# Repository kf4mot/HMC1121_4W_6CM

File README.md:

# HMC1121 4W 6cm
The HMC1121 is a GaAs MMIC 4W power amplifier with an integrated temperature compensated on-chip power detector that operates between 5.5 GHz and 8.5 GHz. The HMC1121 provides 28 dB of gain, 44 dBm output IP3, and 36.5 dBm of saturated output power at 30% PAE from a 7 V power supply.

[Schematic](https://github.com/kf4mot/HMC1121_4W_6CM/blob/master/hardware/HMC1121_4W_6CM.pdf)

[Created with KiCAD ver. 5.1.5-3](https://kicad.org)

[Companion bias board.](https://github.com/kf4mot/Cree_GaN_Driver)

**Things to be done**
- [ ] Add all documentation
- [ ] Revise board for 50Ω traces on better substrate (ro4350).

**Things worth knowing**

1. -To be added.

[Licensed under CERN-OHL-S V2. Julian White, 2020](https://www.ohwr.org/project/cernohl/wikis/home)

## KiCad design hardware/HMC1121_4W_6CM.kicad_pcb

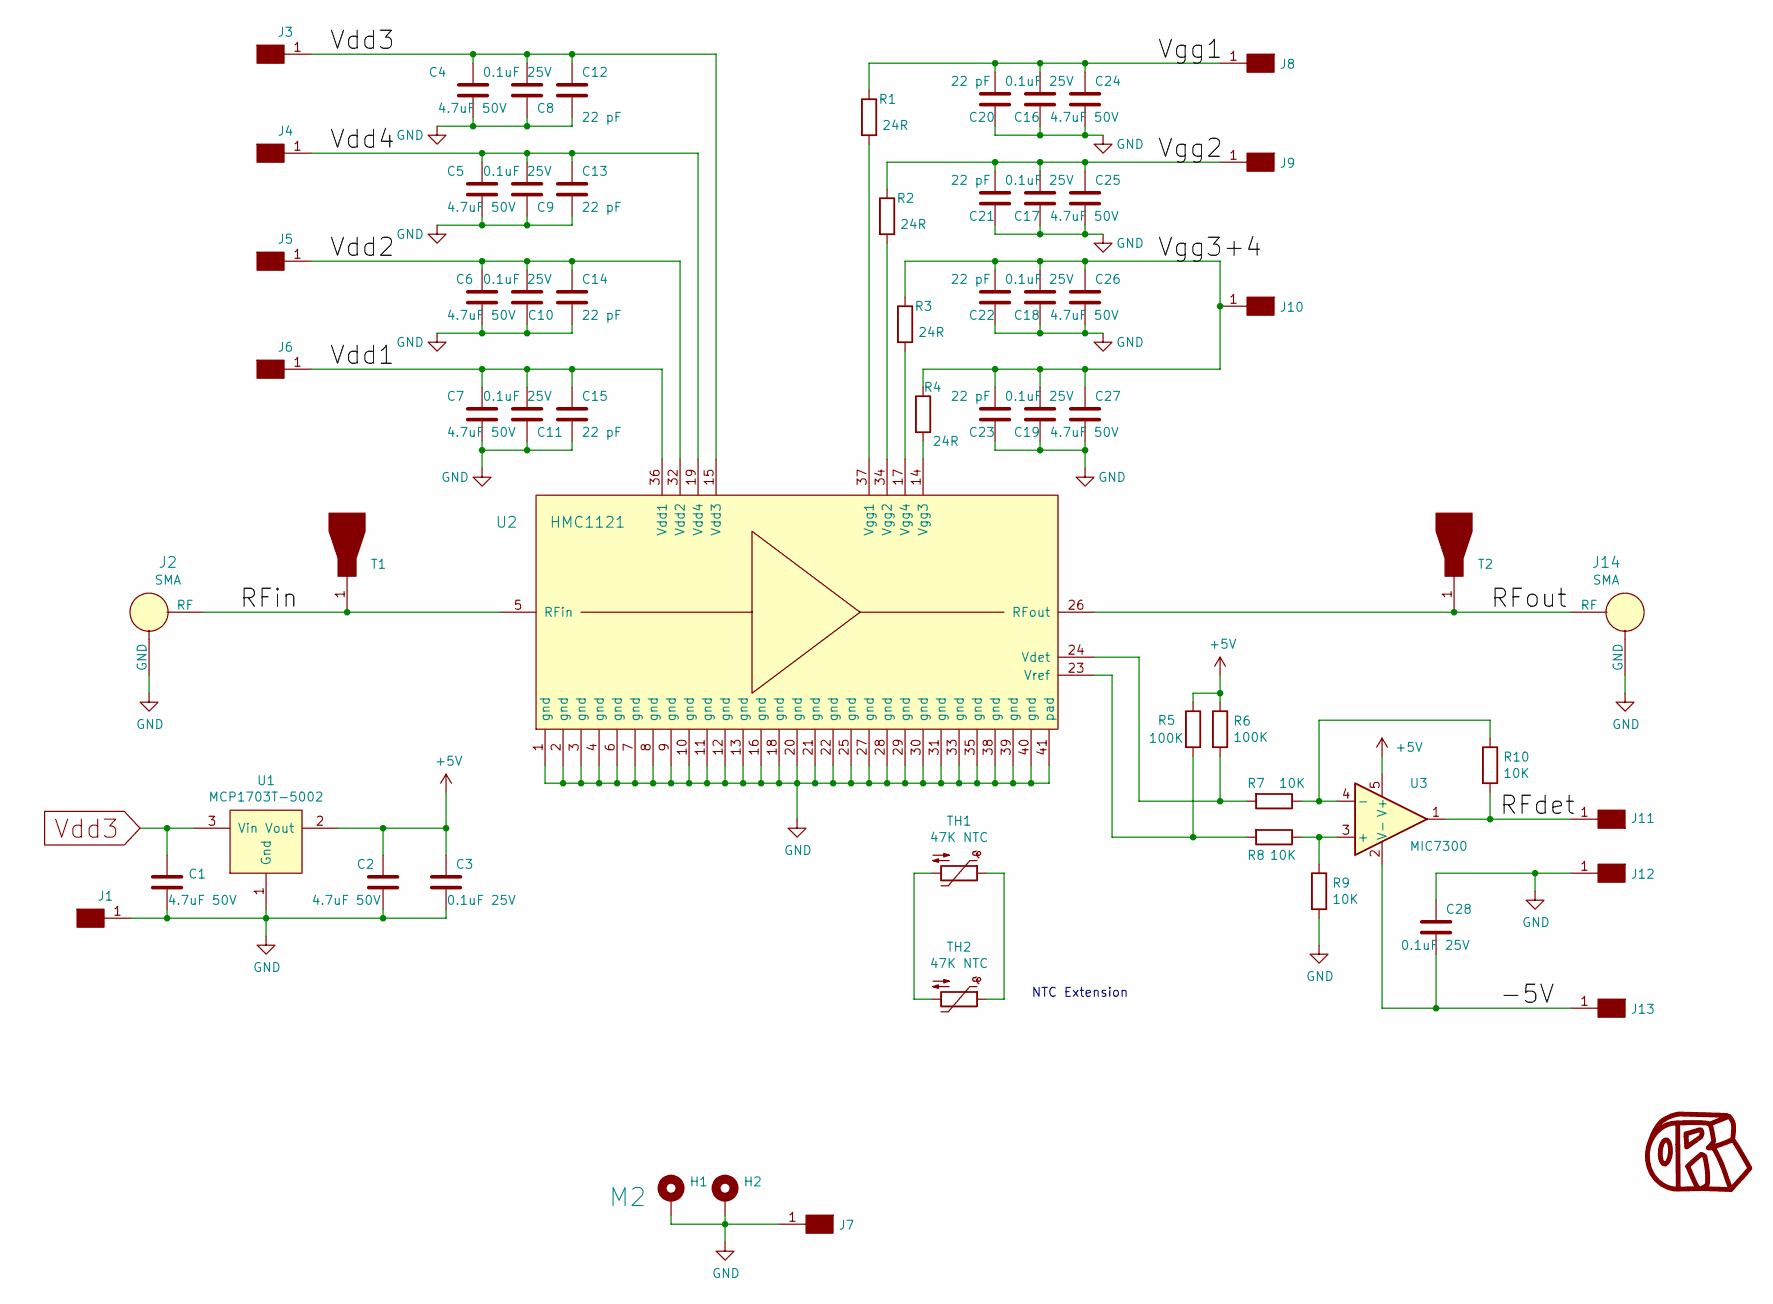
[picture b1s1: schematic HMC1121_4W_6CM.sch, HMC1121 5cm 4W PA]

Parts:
C1, C2, C4, C5, C6, C7, C24, C25, C26, C27: C_4.7uf_50V_x7r_1206; C_1206_3216Metric; Part Number GRM31CR71H475KA12L
C3, C8, C9, C10, C11, C20, C21, C22, C23, C28: 0.1uF_25V_0402_x7r; C_0402_1005Metric; Part Number CGA2B3X7R1E104K050BB
C12, C13, C14, C15, C16, C17, C18, C19: C_22pF_0402_50V_C0G; C_0402_1005Metric; Part Number GRM1555C1H220JA01D
H1, H2: MountingHole_Pad_M2; MountingHole_2.2mm_M2_DIN965_Pad
J1, J3, J4, J5, J6, J7, J8, J9, J10, J11, J12, J13: Conn_4mm_pad; SolderWirePad_single_SMD_4mm
J2, J14: SMA_F_Amp_901-10309; SMA_END_LAUNCH_062_AMP901-10309; Part Number 901-10309
R1, R2, R3, R4: R_24_sm0603; R_0603_1608Metric; Part Number RT0603FRE0724RL
R5, R6: R_100k_sm0603; R_0603; Part Number RT0603FRE07100KL
R7, R8, R9, R10: R_10K_sm0603; R_0603_1608Metric; Part Number RT0603FRE0710KL
T1, T2: Taper_45mil_to_12mil; Taper_45to12_uwT1.14_1.14_0.30_0.30_2.00
TH1, TH2: Thermistor_NTC_ERT-J1VV473J; R_0603_1608Metric; Part Number ERT-J1VV473J
U1: MCP1703T-5002; SOT-23; Part Number MCP1703T-5002E/CB
U2: HMC1121; LFCSP-40-1EP; Part Number HMC1121LP6GE
U3: MIC7300; SOT-23-5; Part Number MIC7300YM5-TR

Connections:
+5V: C2.1, C3.1, R5.1, R6.1, U1.2 (Vout), U3.5 (V+)
/-5V: C28.2, J13.1, U3.2 (V-)
/RFdet: J11.1, R10.2, U3.1
/RFin: J2.1 (RF), T1.1, U2.5 (RFin)
/RFout: J14.1 (RF), T2.1, U2.26 (RFout)
/Vdd1: C7.1, C11.1, C15.1, J6.1, U2.36 (Vdd1)
/Vdd2: C6.1, C10.1, C14.1, J5.1, U2.32 (Vdd2)
/Vdd4: C5.1, C9.1, C13.1, J4.1, U2.19 (Vdd4)
/Vgg1: C16.1, C20.1, C24.1, J8.1, R1.1
/Vgg2: C17.1, C21.1, C25.1, J9.1, R2.1
/Vgg3+4: C18.1, C19.1, C22.1, C23.1, C26.1, C27.1, J10.1, R3.1, R4.1
GND: C1.2, C2.2, C3.2, C4.2, C5.2, C6.2, C7.2, C8.2, C9.2, C10.2, C11.2, C12.2, C13.2, C14.2, C15.2, C16.2, C17.2, C18.2, C19.2, C20.2, C21.2, C22.2, C23.2, C24.2, C25.2, C26.2, C27.2, C28.1, H1.1, H2.1, J1.1, J2.2 (GND), J7.1, J12.1, J14.2 (GND), R9.2, U1.1 (Gnd), U2.1 (gnd), U2.2 (gnd), U2.3 (gnd), U2.4 (gnd), U2.6 (gnd), U2.7 (gnd), U2.8 (gnd), U2.9 (gnd), U2.10 (gnd), U2.11 (gnd), U2.12 (gnd), U2.13 (gnd), U2.16 (gnd), U2.18 (gnd), U2.20 (gnd), U2.21 (gnd), U2.22 (gnd), U2.25 (gnd), U2.27 (gnd), U2.28 (gnd), U2.29 (gnd), U2.30 (gnd), U2.31 (gnd), U2.33 (gnd), U2.35 (gnd), U2.38 (gnd), U2.39 (gnd), U2.40 (gnd), U2.41 (pad)
unnamed: R1.2, U2.37 (Vgg1)
unnamed: R2.2, U2.34 (Vgg2)
unnamed: R3.2, U2.17 (Vgg4)
unnamed: R4.2, U2.14 (Vgg3)
unnamed: R5.2, R8.2, U2.23 (Vref)
unnamed: R6.2, R7.2, U2.24 (Vdet)
unnamed: R8.1, R9.1, U3.3 (+)
unnamed: R7.1, R10.1, U3.4 (-)
unnamed: TH1.1, TH2.1
unnamed: TH1.2, TH2.2
Vdd3: C1.1, C4.1, C8.1, C12.1, J3.1, U1.3 (Vin), U2.15 (Vdd3)

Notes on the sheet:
NTC Extension

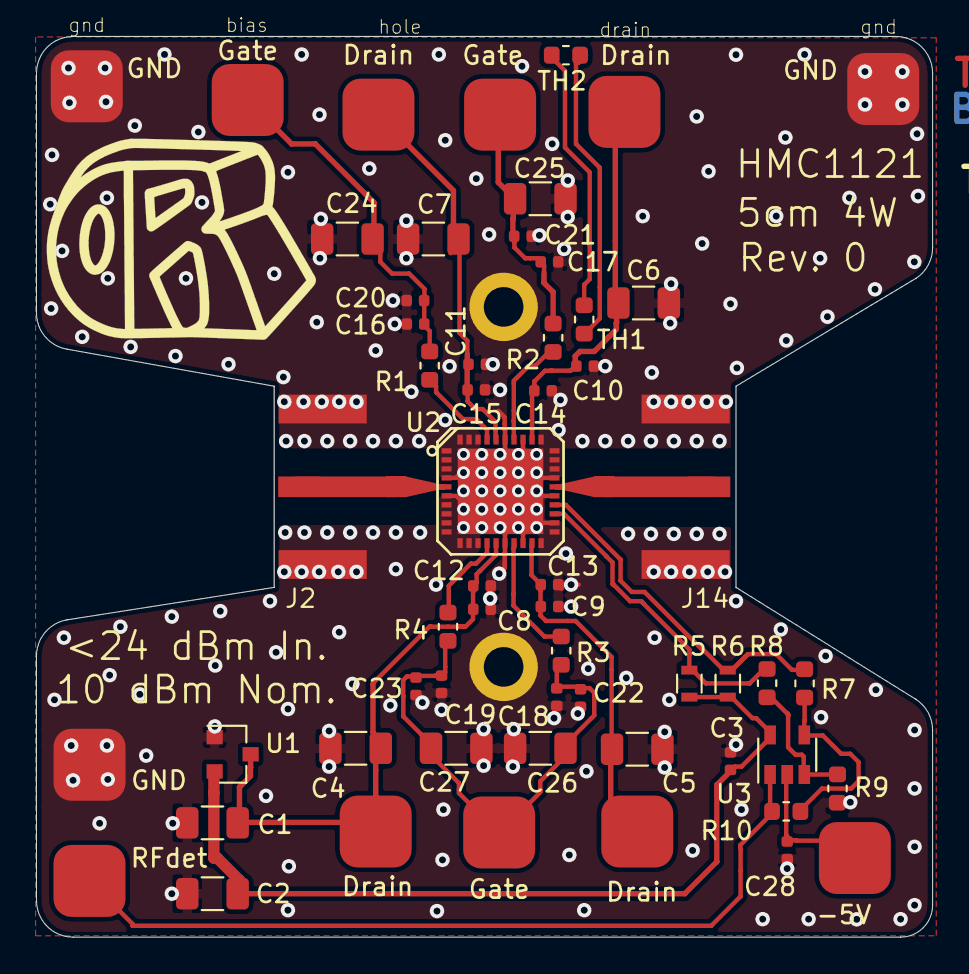
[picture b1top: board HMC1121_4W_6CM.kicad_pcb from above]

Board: 2 copper layers, 49.8 x 50.0 mm, 61 parts (0 on the bottom side), 23 nets.

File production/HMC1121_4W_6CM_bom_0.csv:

Component,Description,Part,References,Value,Footprint,Quantity Per PCB,Datasheet,Part Number,MFG,dsp_value
1,Unpolarized capacitor,0.1uF_25V_0402_x7r,C3 C8 C9 C10 C11 C20 C21 C22 C23 C28,0.1uF_25V_0402_x7r,C_0402_1005Metric,10,~,CGA2B3X7R1E104K050BB,TDK,0.1uF 25V
2,Unpolarized capacitor,C_22pF_0402_50V_C0G,C12 C13 C14 C15 C16 C17 C18 C19,C_22pF_0402_50V_C0G,C_0402_1005Metric,8,https://www.mouser.com/datasheet/2/281/murata_03052018_GRM_S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,GRM1555C1H220JA01D,Murata,22 pF
3,4.7uF 1206 Cap,C_4.7uf_50V_x7r_1206,C1 C2 C4 C5 C6 C7 C24 C25 C26 C27,C_4.7uf_50V_x7r_1206,C_1206_3216Metric,10,https://www.mouser.com/datasheet/2/396/mlcc02_e-1307760.pdf,GRM31CR71H475KA12L,Murata,4.7uF 50V
4,"Generic connector, single row, 01x01",Conn_4mm_pad,J1 J3 J4 J5 J6 J7 J8 J9 J10 J11 J12 J13,Conn_4mm_pad,SolderWirePad_single_SMD_4mm,12,~,,,
5,,SMA_F_Amp_901-10309,J2 J14,SMA_F_Amp_901-10309,SMA_END_LAUNCH_062_AMP901-10309,2,https://www.amphenolrf.com/downloads/dl/file/id/507/product/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,901-10309,Amp,SMA
6,Resistor,R_100k_sm0603,R5 R6,R_100k_sm0603,R_0603,2,https://www.mouser.com/datasheet/2/447/PYu-RT_1-to-0.01_RoHS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,RT0603FRE07100KL,Yageo,100K
7,Resistor,R_10K_sm0603,R7 R8 R9 R10,R_10K_sm0603,R_0603_1608Metric,4,https://www.mouser.com/datasheet/2/427/dcrcwe3-45987.pdf,RT0603FRE0710KL,Yaego,10K
8,Resistor,R_24_sm0603,R1 R2 R3 R4,R_24_sm0603,R_0603_1608Metric,4,https://www.mouser.com/datasheet/2/447/PYu-RT_1-to-0.01_RoHS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,RT0603FRE0724RL,Yageo,24R
9,,Taper_45mil_to_12mil,T1 T2,Taper_45mil_to_12mil,Taper_45to12_uwT1.14_1.14_0.30_0.30_2.00,2,,,,
10,"Temperature dependent resistor, negative temperature coefficient",Thermistor_NTC_ERT-J1VV473J,TH1 TH2,Thermistor_NTC_ERT-J1VV473J,R_0603_1608Metric,2,~,ERT-J1VV473J,Panasonic,47K NTC
11,,HMC1121,U2,HMC1121,LFCSP-40-1EP,1,www.analog.com/media/en/technical-documentation/data-sheets/HMC1121.pdf,HMC1121LP6GE,Analog Devices,
12,,MCP1703T-5002,U1,MCP1703T-5002,SOT-23,1,http://ww1.microchip.com/downloads/en/devicedoc/22049f.pdf,MCP1703T-5002E/CB,Microchip,
13,OPAmp symbol,MIC7300,U3,MIC7300,SOT-23-5,1,http://ww1.microchip.com/downloads/en/DeviceDoc/mic7300.pdf,MIC7300YM5-TR,Microchip,





Component Groups:,13
Component Count:,59
Fitted Components:,59
Number of PCBs:,1
Total components:,59
Schematic Version:,0
Schematic Date:,2019-12-25
BoM Date:,1/7/2020 9:40:04 PM
Schematic Source:,C:\Users\Julian\Documents\kicad_project\HMC1121_4W_6CM\HMC1121_4W_6CM.sch
KiCad Version:,Eeschema (5.1.5)-3

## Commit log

2020-10-15 Update hardware
2021-11-08 Update README.md
    https://forum.kicad.info/t/warning-avoid-all-links-to-kicad-pcb-org-use-kicad-org/31521
